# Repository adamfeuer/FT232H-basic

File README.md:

FT232H-basic
============

This is an FTDI FT232H to USART basic breakout board - it can do USB 2.0 High Speed, and up to 10Mbps 
on the USART interface.

It has USB 2.0 High Speed ESD protection and a resettable fuse on the power input.

This board has been made, tested, and works for send and receive at USB 2.0 HS speeds. 

Known issues
============

TX and RX LEDs did not work on the 0.4.2 version of the board - because the signals are active low,
and needed to be connected to 3.3V via a 470 ohm resistor. This has been fixed.

If you have questions, comments, or improvements, I would love to know them!

cheers<br>
adam<br>
Adam Feuer<br>
Seattle, WA, USA<br>
adam@adamfeuer.com<br>
http://adamfeuer.com<br>

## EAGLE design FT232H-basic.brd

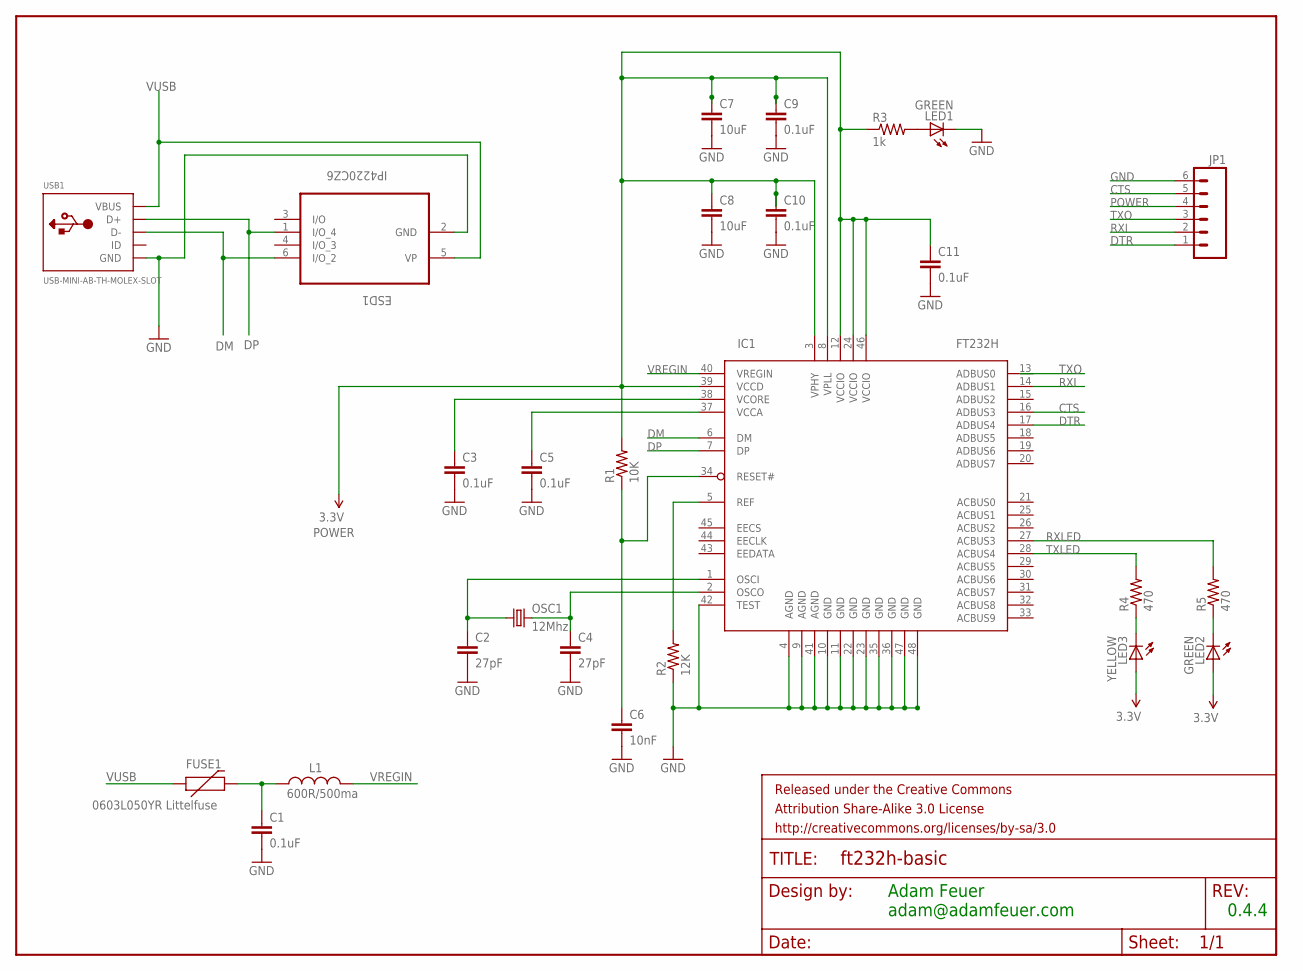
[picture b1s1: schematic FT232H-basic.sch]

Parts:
C1, C3, C5, C9, C10, C11: 0.1uF; 0603-CAP
C2, C4: 27pF; 0603-CAP
C6: 10nF; 0603-CAP
C7, C8: 10uF; 0603-CAP
ESD1: IP4220CZ6; SOT95P275X110-6N
FRAME1: FRAME-LETTER; CREATIVE_COMMONS
FUSE1: 0603L050YR Littelfuse; 0603
IC1: FT232H; LQFP48
JP1: M06SIP; 1X06
L1: 600R/500ma; 0603
LED1, LED2: GREEN; LED-0603
LED3: YELLOW; LED-0603
OSC1: 12Mhz; CRYSTAL-SMD-5X3
R1: 10K; 0603-RES
R2: 12K; 0603-RES
R3: 1k; 0603-RES
R4, R5: 470; 0603-RES
USB1: USB-MINI-AB-TH-MOLEX-SLOT

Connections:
CTS: IC1.16 (ADBUS3), JP1.5
DM: ESD1.6 (I/O_2), IC1.6 (DM), USB1.D-
DP: ESD1.1 (I/O_4), IC1.7 (DP), USB1.D+
DTR: IC1.17 (ADBUS4), JP1.1
GND: C1.2, C2.2, C3.2, C4.2, C5.2, C6.2, C7.2, C8.2, C9.2, C10.2, C11.2, ESD1.2 (GND), IC1.4 (AGND), IC1.9 (AGND), IC1.10 (GND), IC1.11 (GND), IC1.22 (GND), IC1.23 (GND), IC1.35 (GND), IC1.36 (GND), IC1.41 (AGND), IC1.42 (TEST), IC1.47 (GND), IC1.48 (GND), JP1.6, LED1.C, R2.1, USB1.GND
unnamed: C5.1, IC1.37 (VCCA)
unnamed: C3.1, IC1.38 (VCORE)
unnamed: C6.1, IC1.34 (RESET#), R1.1
unnamed: IC1.5 (REF), R2.2
unnamed: LED1.A, R3.2
unnamed: C1.1, FUSE1.2, L1.1
unnamed: C4.1, IC1.2 (OSCO), OSC1.3 (2)
unnamed: LED3.C, R4.1
unnamed: LED2.C, R5.1
OSC1: C2.1, IC1.1 (OSCI), OSC1.1
POWER: C7.1, C8.1, C9.1, C10.1, C11.1, IC1.3 (VPHY), IC1.8 (VPLL), IC1.12 (VCCIO), IC1.24 (VCCIO), IC1.39 (VCCD), IC1.46 (VCCIO), JP1.4, LED2.A, LED3.A, R1.2, R3.1
RXI: IC1.14 (ADBUS1), JP1.2
RXLED: IC1.27 (ACBUS3), R5.2
TXLED: IC1.28 (ACBUS4), R4.2
TXO: IC1.13 (ADBUS0), JP1.3
VREGIN: IC1.40 (VREGIN), L1.2
VUSB: ESD1.5 (VP), FUSE1.1, USB1.VBUS

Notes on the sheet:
Adam Feuer adam@adamfeuer.com
0.4.4

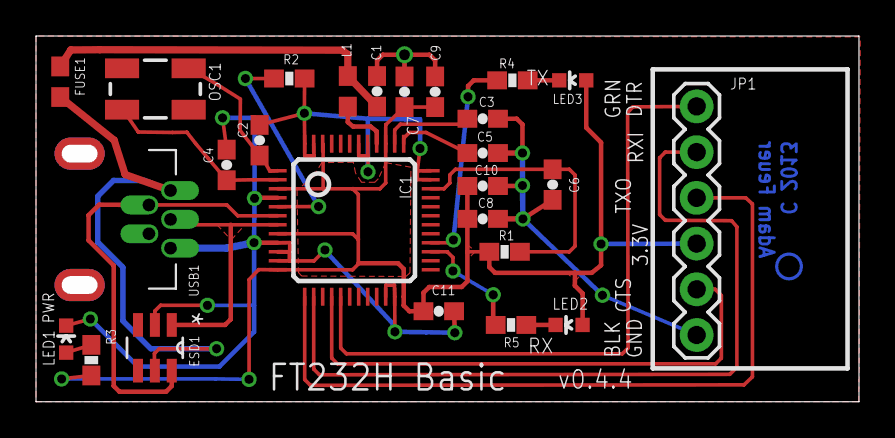
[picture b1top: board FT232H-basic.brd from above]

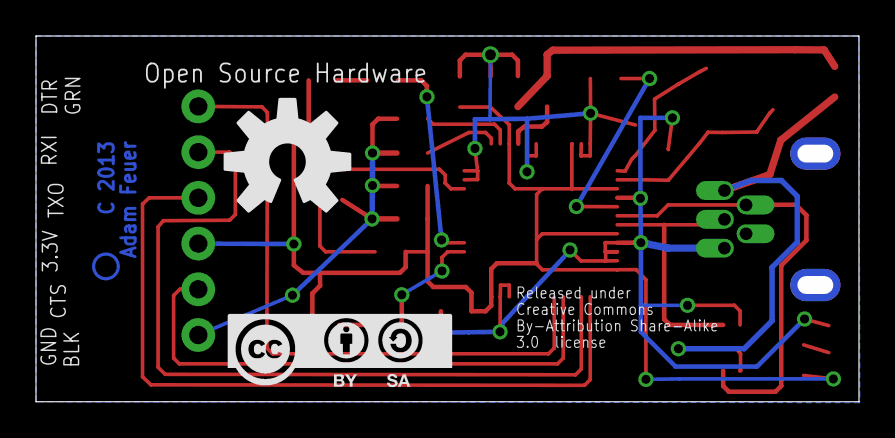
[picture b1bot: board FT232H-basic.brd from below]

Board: 2 copper layers, 45.7 x 20.3 mm, 29 parts (2 on the bottom side), 22 nets.

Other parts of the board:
CC-BY-SA-LOGO: CC-BY-SA
U$1: OSHW-LOGO-L

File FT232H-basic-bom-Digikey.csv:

Digi-Key Part #,Manufacturer,Manufacturer's Part #,Reference,Quantity 1,Quantity 2,Part,Value,Comments,Package,Description,Vendor
399-1282-1-ND,,,,5,,C1,0.1uF,0.1UF-25V-5%(0603),0603-CAP,CAP-08604,Digikey
MCT0603-10.0K-MFCT-ND,,,,1,,R1,10K,10KOHM1/10W1%(0603)0603,0603-RES,RES-00824,Digikey
399-7839-1-ND ,,,,1,,C6,10nF,0.1UF-25V-5%(0603),0603-CAP,CAP-08604,Digikey
1276-1869-1-ND,,,,2,,C7,10uF,0.1UF-25V-5%(0603),0603-CAP,CAP-08604,Digikey
541-12.0KHCT-ND,,,,1,,R2,12K,RESISTOR0603,0603-RES,Resistor,Digikey
887-1292-2-ND ,,,,1,,OSC1,12Mhz,CRYSTAL5X3,CRYSTAL-SMD-5X3,Various standard crystals. Proven footprints. Spark Fun Electronics SKU : COM-00534,Digikey
MCT0603-1.00K-MFCT-ND,,,,3,,R3,1k,1K-1%,0603-RES,1k-ohm SMT,Digikey
399-9053-1-ND,,,,2,,C2,27pF,0.1UF-25V-5%(0603),0603-CAP,CAP-08604,Digikey
445-6157-1-ND,,,,1,,L1,600R/500ma,INDUCTOR0603,603,Inductors,Digikey
768-1101-1-ND,,,,1,,IC1,FT232H,FT232H,LQFP48,FTDI FT232H,Digikey
160-1183-2-ND,,,,2,,LED1,GREEN,LED-GREEN0603,LED-0603,Various green LEDs,Digikey
568-3529-1-ND ,,,,1,,ESD1,IP4220CZ6,IP4220CZ6,SSOT-6,IP4220CZ6 - USB HS ESD protection,Digikey
160-1184-2-ND ,,,,1,,LED3,YELLOW,LED-YELLOW0603,LED-0603,Yellow SMD LEDs,Digikey
NA,,,,1,,JP1,,M06SMD-FEMALE-V2,1X06-SMD-FEMALE-V2,Header 6,Sparkfun
WM17121-ND,Molex,,,1,,USB1,,USB-MINIBTH-SLOT,USB-MINI-AB-TH-MOLEX-SLOT,USB Connectors,Digikey
F2112CT-ND ,Littelfuse,,,1,,F1,,1206L050YR Littelfuse,PTC0603,Resettable Fuse,Digikey

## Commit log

2013-08-16 initial addition of schematic for FT232H basic board
2013-08-17 initial addition of board file - board fully routed, but still a mess
2013-08-21 routing improvements - much simpler, has bottom ground plane and top copper pour
2013-08-21 board is slightly smaller now; traces in ground plane shorter
2013-08-22 board is slightly smaller again, using space under TTL connector for traces
2013-08-22 reduced board width
2013-08-23 board routed, passes DRC, and has silkscreen; not all fonts are vector
2013-08-23 added cam and dru files
2013-08-23 changed all fonts to vector (by smashing all parts)
2013-08-28 minor changes - removed CC logo from schematic (still on board); made layers visible
2013-08-28 added OSH Park packaging script
2013-08-28 added eagle.epf file
2013-08-28 added creative commons logo files
2013-08-28 added CC-BY-SA 3.0 License text and url
2013-08-28 updated Readme with untested and contact info
2013-08-28 updated markdown formatting in Readme
2013-08-29 adding schematic pdf
2013-08-29 added note about 1x6 surface mount female header availability
2013-08-29 updated README file with comment about ESD chip not good for USB 2.0
2013-08-30 changed out ESD IC to USB 2.0 HS - NXP IP4220CZ6 ; added LittelFuse 0603; changed out connector to 1x06 female through hole
2013-08-30 updated PDF schematic and readme
2013-08-31 added bounding box for 1x06 female header
2013-09-05 after v0.1 back from OSH Park: made part names larger, bumped version to 0.3
2013-09-05 moved USB connector name to be actually on the board
2013-09-06 minor update to readme
2013-09-06 board passes ERC
2013-09-06 added nxp-IP4220CZ6 ESD protection IC library
2013-09-06 added Digikey BOMs
2013-09-06 minor changes to silkscreen
2013-09-07 rerouted USART traces to keep them on top side of board, shortened paths - for high speed routing
2013-09-07 rerouted USB DP and DM traces to make them more direct - for high speed routing
2013-09-07 rerouted USB DP and DM traces to be entirely on top of board, with shorter paths
2013-09-07 updated schematic to reflect correct size 0603 of FUSE1
2013-09-08 rerouted board to make USB DM and DP signals as short as possible; USART data signals are on top of board; board is slightly wider; version bumped to 0.4
2013-09-08 fixed error with TX LED being in wrong place - power LED is now in lower left, TX in upper right-middle
2013-09-08 minor cosmetic changes to polygons
2013-09-09 replaced decoupling capacitors close to chip; rerouted board
2013-09-09 moved OSC1 traces so they are not serpentine
2013-09-13 moved VUSB trace so it doesn't cross under USB DP and DM - so there is only ground plane under the high speed traces
2013-10-02 updated readme to say board is tested
2013-10-02 minor updates to board legend; added BOM files and board PDF
2013-10-04 fixed TX/RX led bug - TX/RX signals are active low, so need to be connected to power via 47O ohm resistor, as per UM232H datasheet
2013-10-04 updated readme re: fixed TX/RX LEDS
2013-10-05 updated PDFs
2013-11-10 fixed LED orientation - anode faces power
2013-11-25 added .gitignore
2013-11-25 updated bom spreadsheet
2013-12-24 corrected RX and TX LED circuit

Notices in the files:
FT232H-basic.brd:
Released under
Creative Commons
By-Attribution Share-Alike
parts and their libraries:
SparkFun-Capacitors: Licensing: CC v3.0 Share-Alike You are welcome to use this library for commercial purposes.
SparkFun-Aesthetics: Released under the Creative Commons Attribution Share-Alike 3.0 License
SparkFun-Aesthetics: http://creativecommons.org/licenses/by-sa/3.0
